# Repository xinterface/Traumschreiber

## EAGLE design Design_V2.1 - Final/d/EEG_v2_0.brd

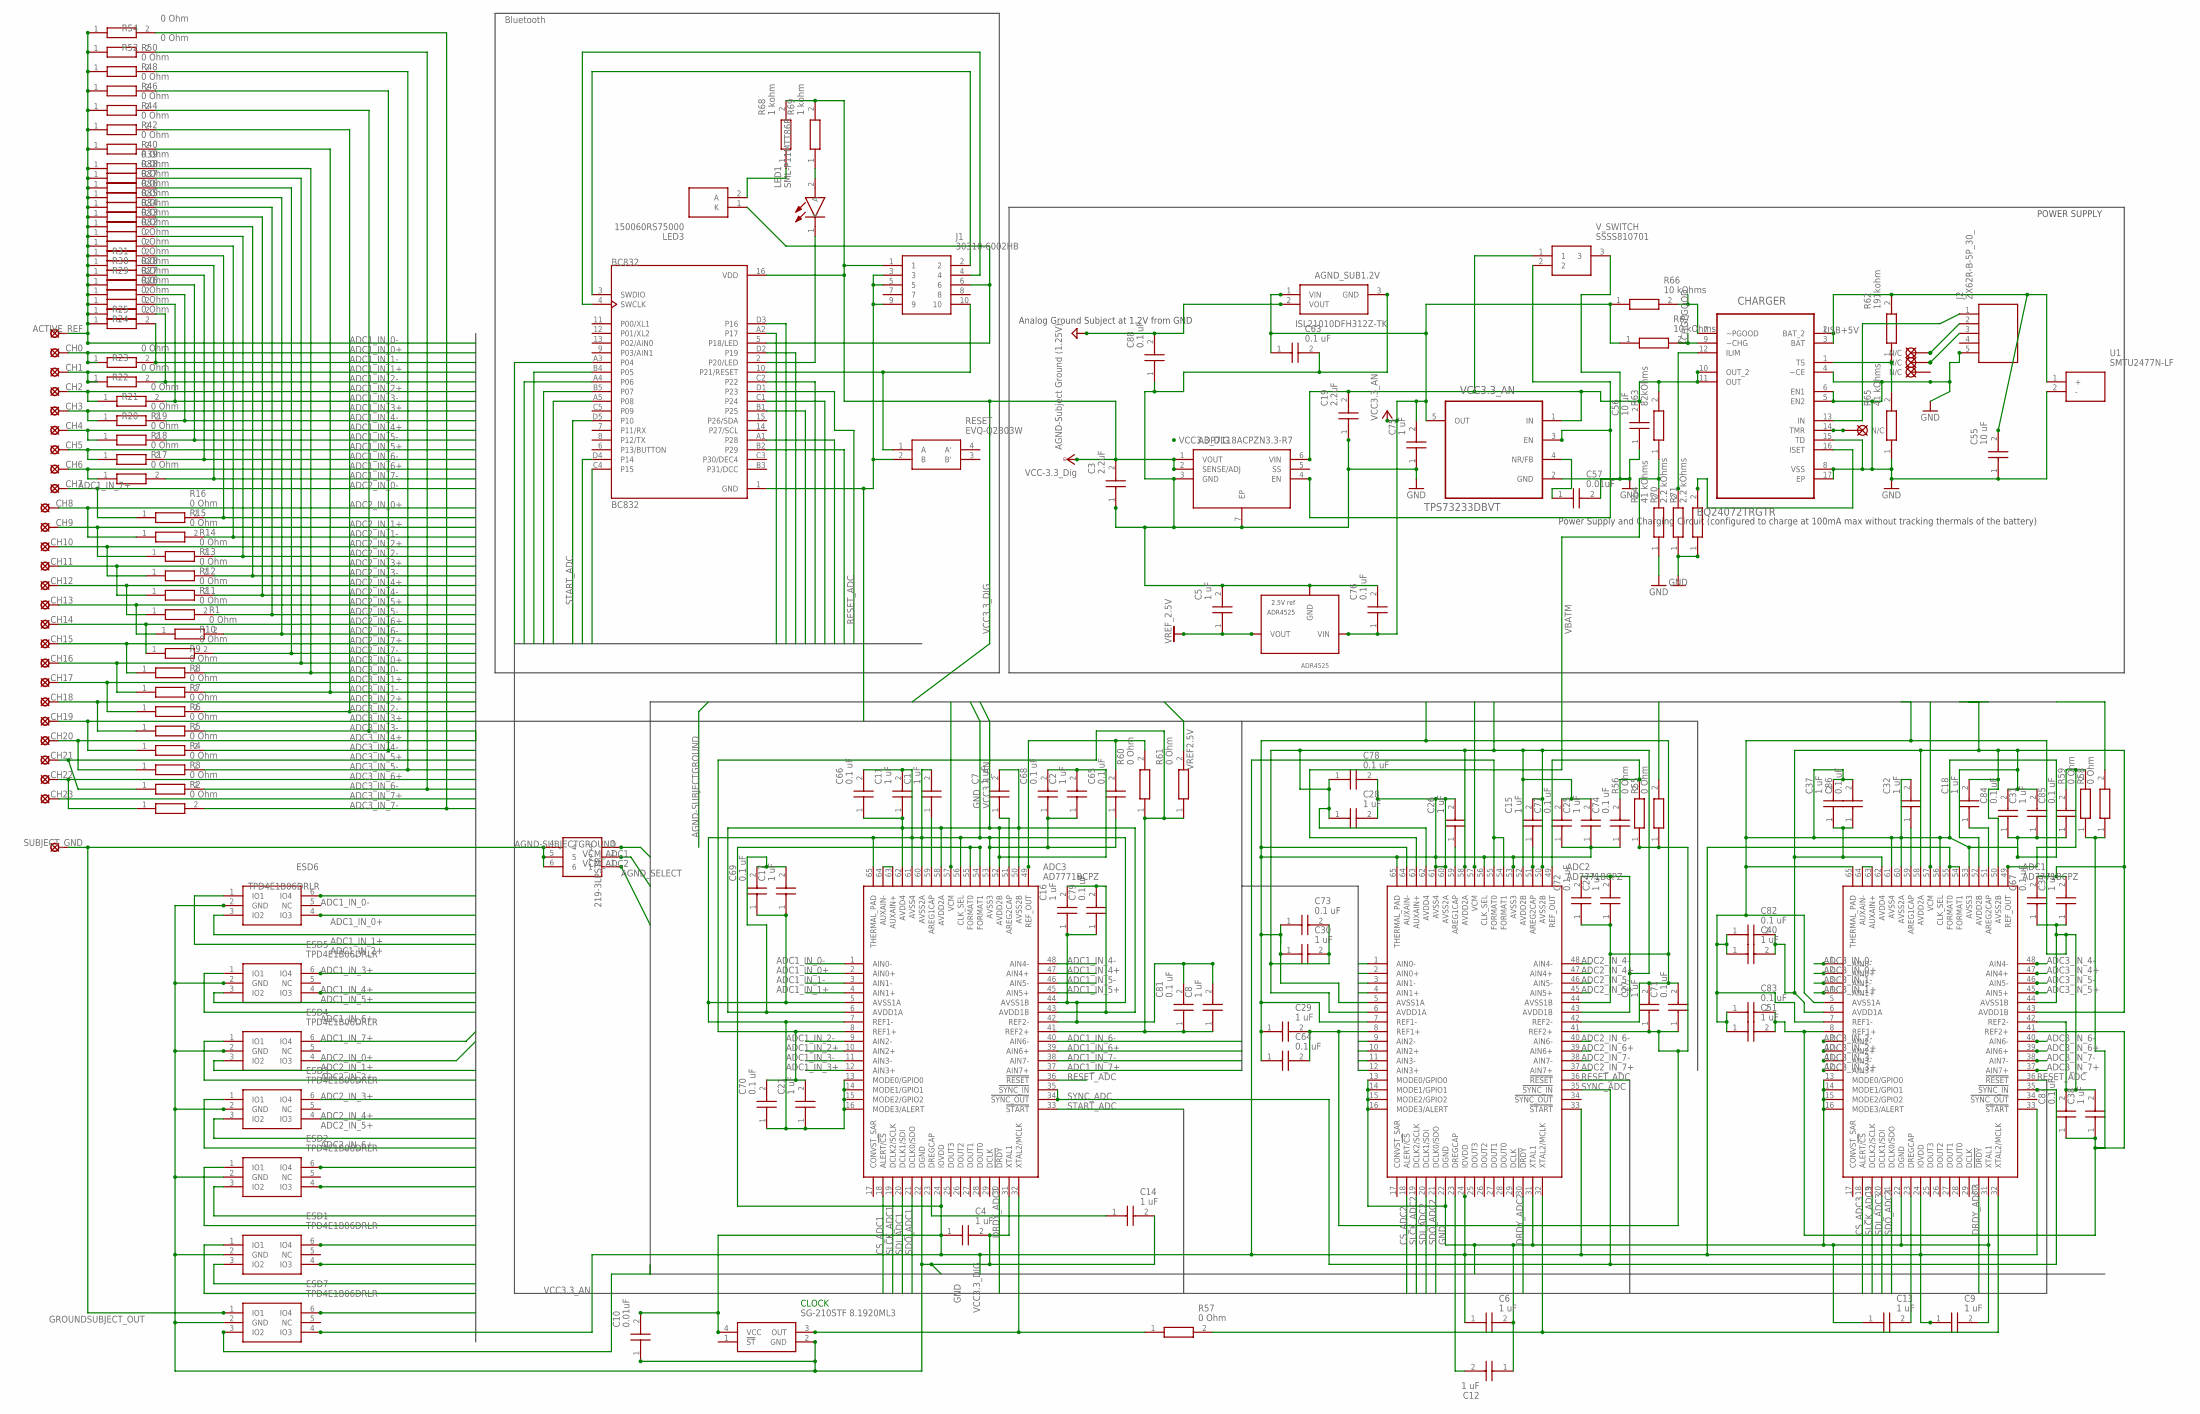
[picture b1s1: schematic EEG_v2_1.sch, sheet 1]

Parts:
ACTIVE_REF: SE11
ADC1, ADC2, ADC3: AD7771BCPZ; QFN50P900X900X80-65N
ADR4525: ADR4525; SOIC-8
AGND_SELECT: 219-3LPSTR; 2193LPSTR
AGND_SUB1.2V: ISL21010DFH312Z-TK; SOT95P237X112-3N
BC832: BC832; XCVR_BC832
C1, C2, C4, C5, C6, C7, C8, C9, C11, C12, C13, C14, C15, C16, C17, C18, C21, C24, C25, C26, C27, C28, C29, C30, C31, C32, C37, C38, C39, C40, C51: 1 uF; CAPC1005X33N
C3, C19: 2.2uF; CAPC0603X33N
C10, C57: 0.01uF; CAPC0402X22N
C55, C56: 10 uF; CAPC1608X100N
C63, C64, C65, C66, C67, C68, C69, C70, C71, C72, C73, C74, C76, C77, C78, C79, C81, C82, C83, C84, C85, C86, C87, C88: 0.1 uF; CAPC0402X22N
C75: 1 uF; CAPC0402X22N
CH0, CH1, CH2, CH3, CH4, CH5, CH6, CH7, CH8, CH9, CH10, CH11, CH12, CH13, CH14, CH15, CH16, CH17, CH18, CH19, CH20, CH21, CH22, CH23: SE11
CHARGER: BQ24072TRGTR; QFN50P300X300X100-17N
CLOCK: SG-210STF 8.1920ML3; SG-210STF8.1920ML
ESD1, ESD2, ESD3, ESD4, ESD5, ESD6, ESD7: TPD4E1B06DRLR; SOP50P160X60-6N
J1: 30310-6002HB; SHDR10W64P254_2X5_2030X878X930
J2: ZX62R-B-5P_30_; ZX62R-B-5P(30)
LED1: SML-P11MTT86R; LEDC1006X25N
LED3: 150060RS75000; LEDC1608X80N
R1, R2, R3, R4, R5, R6, R7, R8, R9, R10, R11, R12, R13, R14, R15, R16, R17, R18, R19, R20, R21, R22, R23, R24, R25, R26, R27, R28, R29, R30, R31, R32, R33, R34, R35, R36, R37, R38, R39, R40, R42, R44, R46, R48, R50, R52, R54, R55, R56, R57, R58, R59, R60, R61: 0 Ohm; RESC1608X55N
R62: 191kohm; RESC0603X26N
R63: 82kOhms; RESC1608X55N
R64, R65: 41 kOhms; RESC0603X28N
R66, R67: 10 kOhms; RESC0402X15N
R68, R69: 1 kohm; RESC0603X26N
R70, R71: 2.2 kOhms; RESC3225X70N
RESET: EVQ-Q2B03W; EVQQ2
SUBJECT_GND: SE11
U1: SMTU2477N-LF; SMTU2477NLF
VCC3.3_AN: TPS73233DBVT; SOT95P280X145-5N
VCC3.3_DIG: ADP7118ACPZN3.3-R7; SON65P200X200X65-7N
V_SWITCH: SSSS810701

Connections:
-CHG: CHARGER.9 (~CHG), R67.2
-PGOOD: CHARGER.7 (~PGOOD), R66.2
ADC1_IN_0+: ADC3.2 (AIN0+), CH0.MP, ESD6.4 (IO3), R23.1
ADC1_IN_0-: ACTIVE_REF.MP, ADC3.1 (AIN0-), ESD6.6 (IO4), R24.1, R25.1, R26.1, R27.1, R28.1, R29.1, R30.1, R31.1, R32.1, R33.1, R34.1, R35.1, R36.1, R37.1, R38.1, R39.1, R40.1, R42.1, R44.1, R46.1, R48.1, R50.1, R52.1, R54.1
ADC1_IN_1+: ADC3.4 (AIN1+), CH1.MP, ESD6.3 (IO2), R22.1
ADC1_IN_1-: ADC3.3 (AIN1-), R23.2, R24.2
ADC1_IN_2+: ADC3.10 (AIN2+), CH2.MP, ESD6.1 (IO1), R21.1
ADC1_IN_2-: ADC3.9 (AIN2-), R22.2, R25.2
ADC1_IN_3+: ADC3.12 (AIN3+), CH3.MP, ESD5.6 (IO4), R20.1
ADC1_IN_3-: ADC3.11 (AIN3-), R21.2, R26.2
ADC1_IN_4+: ADC3.47 (AIN4+), CH4.MP, ESD5.4 (IO3), R19.1
ADC1_IN_4-: ADC3.48 (AIN4-), R20.2, R27.2
ADC1_IN_5+: ADC3.45 (AIN5+), CH5.MP, ESD5.3 (IO2), R18.1
ADC1_IN_5-: ADC3.46 (AIN5-), R19.2, R28.2
ADC1_IN_6+: ADC3.39 (AIN6+), CH6.MP, ESD5.1 (IO1), R17.1
ADC1_IN_6-: ADC3.40 (AIN6-), R18.2, R29.2
ADC1_IN_7+: ADC3.37 (AIN7+), CH7.MP, ESD4.4 (IO3), R16.1
ADC1_IN_7-: ADC3.38 (AIN7-), R17.2, R30.2
ADC2_IN_0+: ADC2.2 (AIN0+), CH8.MP, ESD4.6 (IO4), R15.1
ADC2_IN_0-: ADC2.1 (AIN0-), R16.2, R31.2
ADC2_IN_1+: ADC2.4 (AIN1+), CH9.MP, ESD4.3 (IO2), R14.1
ADC2_IN_1-: ADC2.3 (AIN1-), R15.2, R32.2
ADC2_IN_2+: ADC2.10 (AIN2+), CH10.MP, ESD4.1 (IO1), R13.1
ADC2_IN_2-: ADC2.9 (AIN2-), R14.2, R33.2
ADC2_IN_3+: ADC2.12 (AIN3+), CH11.MP, ESD3.4 (IO3), R12.1
ADC2_IN_3-: ADC2.11 (AIN3-), R13.2, R34.2
ADC2_IN_4+: ADC2.47 (AIN4+), CH12.MP, ESD3.6 (IO4), R11.1
ADC2_IN_4-: ADC2.48 (AIN4-), R12.2, R35.2
ADC2_IN_5+: ADC2.45 (AIN5+), CH13.MP, ESD3.3 (IO2), R1.1
ADC2_IN_5-: ADC2.46 (AIN5-), R11.2, R36.2
ADC2_IN_6+: ADC2.39 (AIN6+), CH14.MP, ESD3.1 (IO1), R10.1
ADC2_IN_6-: ADC2.40 (AIN6-), R1.2, R37.2
ADC2_IN_7+: ADC2.37 (AIN7+), CH15.MP, ESD2.6 (IO4), R9.1
ADC2_IN_7-: ADC2.38 (AIN7-), R10.2, R38.2
ADC3_IN_0+: ADC1.2 (AIN0+), CH16.MP, ESD2.4 (IO3), R8.1, R39.2
ADC3_IN_0-: ADC1.1 (AIN0-), R9.2, R40.2
ADC3_IN_1+: ADC1.4 (AIN1+), CH17.MP, ESD2.3 (IO2), R7.1
ADC3_IN_1-: ADC1.3 (AIN1-), R8.2, R42.2
ADC3_IN_2+: ADC1.10 (AIN2+), CH18.MP, ESD2.1 (IO1), R6.1
ADC3_IN_2-: ADC1.9 (AIN2-), R7.2, R44.2
ADC3_IN_3+: ADC1.12 (AIN3+), CH19.MP, ESD1.6 (IO4), R5.1
ADC3_IN_3-: ADC1.11 (AIN3-), R6.2, R46.2
ADC3_IN_4+: ADC1.47 (AIN4+), CH20.MP, ESD1.4 (IO3), R4.1
ADC3_IN_4-: ADC1.48 (AIN4-), R5.2, R48.2
ADC3_IN_5+: ADC1.45 (AIN5+), CH21.MP, ESD1.3 (IO2), R3.1
ADC3_IN_5-: ADC1.46 (AIN5-), R4.2, R50.2
ADC3_IN_6+: ADC1.39 (AIN6+), CH22.MP, ESD1.1 (IO1), R2.1
ADC3_IN_6-: ADC1.40 (AIN6-), R3.2, R52.2
ADC3_IN_7+: ADC1.37 (AIN7+), CH23.MP, ESD7.6 (IO4)
ADC3_IN_7-: ADC1.38 (AIN7-), R2.2, R54.2
AGND-SUBJECTGROUND: AGND_SELECT.3, AGND_SUB1.2V.2 (VOUT), C88.2
CS_ADC1: ADC3.18 (ALERT/!CS), BC832.A4 (P06)
CS_ADC2: ADC2.18 (ALERT/!CS), BC832.A5 (P08)
CS_ADC3: ADC1.18 (ALERT/!CS), BC832.C1 (P24)
DRDY_ADC1: ADC3.30 (!DRDY), BC832.A2 (P17)
DRDY_ADC2: ADC2.30 (!DRDY), BC832.D4 (P14)
DRDY_ADC3: ADC1.30 (!DRDY), BC832.B1 (P25)
GND: ADC1.5 (AVSS1A), ADC1.7 (REF1-), ADC1.13 (MODE0/GPIO0), ADC1.14 (MODE1/GPIO1), ADC1.15 (MODE2/GPIO2), ADC1.16 (MODE3/ALERT), ADC1.22 (DGND), ADC1.31 (XTAL1), ADC1.42 (REF2-), ADC1.44 (AVSS1B), ADC1.53 (AVSS3), ADC1.56 (CLK_SEL), ADC1.60 (AVSS2A), ADC1.61 (AVSS4), ADC1.65 (THERMAL_PAD), ADC2.5 (AVSS1A), ADC2.7 (REF1-), ADC2.13 (MODE0/GPIO0), ADC2.14 (MODE1/GPIO1), ADC2.15 (MODE2/GPIO2), ADC2.16 (MODE3/ALERT), ADC2.22 (DGND), ADC2.31 (XTAL1), ADC2.42 (REF2-), ADC2.44 (AVSS1B), ADC2.53 (AVSS3), ADC2.56 (CLK_SEL), ADC2.60 (AVSS2A), ADC2.61 (AVSS4), ADC2.64 (AUXAIN-), ADC2.65 (THERMAL_PAD), ADC3.5 (AVSS1A), ADC3.7 (REF1-), ADC3.13 (MODE0/GPIO0), ADC3.14 (MODE1/GPIO1), ADC3.15 (MODE2/GPIO2), ADC3.16 (MODE3/ALERT), ADC3.22 (DGND), ADC3.31 (XTAL1), ADC3.42 (REF2-), ADC3.44 (AVSS1B), ADC3.53 (AVSS3), ADC3.56 (CLK_SEL), ADC3.60 (AVSS2A), ADC3.61 (AVSS4), ADC3.65 (THERMAL_PAD), ADR4525.4 (GND), AGND_SUB1.2V.3 (GND), BC832.1 (GND), C1.2, C2.1, C3.1, C4.2, C5.2, C6.2, C8.2, C9.2, C10.1, C11.2, C12.1, C13.1, C14.2, C16.1, C17.1, C19.1, C21.1, C24.1, C25.1, C26.2, C27.2, C28.2, C29.1, C30.1, C31.1, C32.2, C37.2, C38.2, C39.1, C40.1, C51.1, C55.1, C56.1, C57.2, C63.2, C64.1, C65.1, C66.2, C67.1, C68.1, C69.1, C70.1, C71.2, C72.1, C73.1, C74.1, C75.1, C76.2, C77.1, C78.2, C79.1, C81.2, C82.1, C83.1, C84.1, C85.1, C86.2, C87.2, C88.1, CHARGER.4 (~CE), CHARGER.5 (EN2), CHARGER.6 (EN1), CHARGER.8 (VSS), CHARGER.15 (TD), CHARGER.17 (EP), CLOCK.2 (GND), ESD1.2 (GND), ESD2.2 (GND), ESD3.2 (GND), ESD4.2 (GND), ESD5.2 (GND), ESD6.2 (GND), ESD7.2 (GND), J1.3, J1.5, J1.9, J2.5, R64.1, R65.1, R70.1, R71.1, RESET.2 (B), U1.2 (-), VCC3.3_AN.2 (GND), VCC3.3_DIG.3 (GND), VCC3.3_DIG.7 (EP), V_SWITCH.3; also elsewhere on the board
GROUNDSUBJECT_OUT: AGND_SELECT.4, AGND_SELECT.5, AGND_SELECT.6, ESD7.1 (IO1), SUBJECT_GND.MP
unnamed: ADC3.59 (AREG1CAP), C1.1
unnamed: ADC2.23 (DREGCAP), C12.2
unnamed: ADC2.49 (REF_OUT), C74.2, R56.2
unnamed: ADC1.49 (REF_OUT), C85.2, R59.2
unnamed: BC832.5 (P18/LED), J1.6, LED3.1 (K)
unnamed: BC832.2 (P20/LED), LED1.1 (K)
unnamed: ADC3.63 (AUXAIN+), ADC3.64 (AUXAIN-)
unnamed: ADC3.51 (AREG2CAP), C7.1
unnamed: VCC3.3_AN.3 (EN), VCC3.3_DIG.4 (EN), V_SWITCH.2
unnamed: LED3.2 (A), R68.1
unnamed: LED1.2 (A), R69.1
unnamed: BC832.3 (SWDIO), J1.2
unnamed: ADC2.51 (AREG2CAP), C15.1
unnamed: ADC3.23 (DREGCAP), C14.1
unnamed: BC832.4 (SWCLK), J1.4
unnamed: ADC1.23 (DREGCAP), C13.2
unnamed: BC832.10 (P21/RESET), J1.10, RESET.1 (A)
unnamed: C19.2, C56.2, CHARGER.10 (OUT_2), CHARGER.11 (OUT), R63.2, VCC3.3_AN.1 (IN), VCC3.3_DIG.6 (VIN), V_SWITCH.1
unnamed: C57.1, VCC3.3_AN.4 (NR/FB)
unnamed: ADC1.63 (AUXAIN+), ADC1.64 (AUXAIN-)
unnamed: ADC1.59 (AREG1CAP), C32.1
unnamed: ADC2.59 (AREG1CAP), C26.1
unnamed: ADC1.51 (AREG2CAP), C18.1
unnamed: ADC2.8 (REF1+), ADC2.41 (REF2+), C27.1, C29.2, C64.2, C71.1, R55.1, R56.1
unnamed: ADC1.8 (REF1+), ADC1.41 (REF2+), C38.1, C51.2, C83.2, C87.1, R58.1, R59.1
unnamed: CHARGER.1 (TS), R62.1, R65.2
unnamed 86: C55.2, CHARGER.2 (BAT_2), CHARGER.3 (BAT), R62.2, U1.1 (+); also elsewhere on the board
unnamed: CHARGER.16 (ISET), R71.2
unnamed: CHARGER.12 (ILIM), R70.2
REF_ADC1_IN: ADC3.8 (REF1+), ADC3.41 (REF2+), C8.1, C21.2, C70.2, C81.1, R60.1, R61.1
REF_ADC1_OUT: ADC3.49 (REF_OUT), C65.2, R60.2
RESET_ADC: ADC1.36 (!RESET), ADC2.36 (!RESET), ADC3.36 (!RESET), BC832.D1 (P23)
SDI_ADC1: ADC3.20 (DCLK1/SDI), BC832.C4 (P15)
SDI_ADC2: ADC2.20 (DCLK1/SDI), BC832.B5 (P07)
SDI_ADC3: ADC1.20 (DCLK1/SDI), BC832.A1 (P28)
SDO_ADC1: ADC3.21 (DCLK0/SDO), BC832.D3 (P16)
SDO_ADC2: ADC2.21 (DCLK0/SDO), BC832.B4 (P05)
SDO_ADC3: ADC1.21 (DCLK0/SDO), BC832.B2 (P29)
SLCK_ADC1: ADC3.19 (DCLK2/SCLK), BC832.A3 (P04)
SLCK_ADC2: ADC2.19 (DCLK2/SCLK), BC832.D2 (P19)
SLCK_ADC3: ADC1.19 (DCLK2/SCLK), BC832.C2 (P22)
START_ADC: ADC3.33 (!START), BC832.D5 (P10)
SYNC_ADC: ADC1.35 (!SYNC_IN), ADC2.35 (!SYNC_IN), ADC3.34 (!SYNC_OUT), ADC3.35 (!SYNC_IN)
USB+5V: CHARGER.13 (IN), J2.1; also elsewhere on the board
VBATM: ADC2.63 (AUXAIN+), R63.1, R64.2
VCC3.3_AN: ADC1.6 (AVDD1A), ADC1.43 (AVDD1B), ADC1.50 (AVSS2B), ADC1.52 (AVDD2B), ADC1.58 (AVDD2A), ADC1.62 (AVDD4), ADC2.6 (AVDD1A), ADC2.43 (AVDD1B), ADC2.50 (AVSS2B), ADC2.52 (AVDD2B), ADC2.58 (AVDD2A), ADC2.62 (AVDD4), ADC3.6 (AVDD1A), ADC3.43 (AVDD1B), ADC3.50 (AVSS2B), ADC3.52 (AVDD2B), ADC3.58 (AVDD2A), ADC3.62 (AVDD4), ADR4525.2 (VIN), AGND_SUB1.2V.1 (VIN), C2.2, C7.2, C11.1, C15.2, C16.2, C17.2, C18.2, C24.2, C25.2, C28.1, C30.2, C31.2, C37.1, C39.2, C40.2, C63.1, C66.1, C67.2, C68.2, C69.2, C72.2, C73.2, C75.2, C76.1, C77.2, C78.1, C79.2, C82.2, C84.2, C86.1, ESD7.3 (IO2), R66.1, R67.1, VCC3.3_AN.5 (OUT)
VCC3.3_DIG: ADC1.24 (IOVDD), ADC1.33 (!START), ADC1.54 (FORMAT1), ADC1.55 (FORMAT0), ADC2.24 (IOVDD), ADC2.33 (!START), ADC2.54 (FORMAT1), ADC2.55 (FORMAT0), ADC3.24 (IOVDD), ADC3.54 (FORMAT1), ADC3.55 (FORMAT0), BC832.16 (VDD), C3.2, C4.1, C6.1, C9.1, C10.2, CLOCK.4 (VCC), ESD7.4 (IO3), J1.1, R68.2, R69.2, VCC3.3_DIG.1 (VOUT), VCC3.3_DIG.2 (SENSE/ADJ)
VCM_ADC1: ADC3.57 (VCM), AGND_SELECT.2
VCM_ADC2: ADC2.57 (VCM), AGND_SELECT.1
VCM_ADC3: ADC1.57 (VCM)
VREF2.5V: ADR4525.6 (VOUT), C5.1, R55.2, R58.2, R61.2
XTAL_OUT: ADC3.32 (XTAL2/MCLK), CLOCK.3 (OUT), R57.1
XTAL_OUT_SWITCHED: ADC1.32 (XTAL2/MCLK), ADC2.32 (XTAL2/MCLK), R57.2

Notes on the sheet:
Analog Ground Subject at 1.2V from GND
Power Supply and Charging Circuit (configured to charge at 100mA max without tracking thermals of the battery)
POWER SUPPLY
Bluetooth

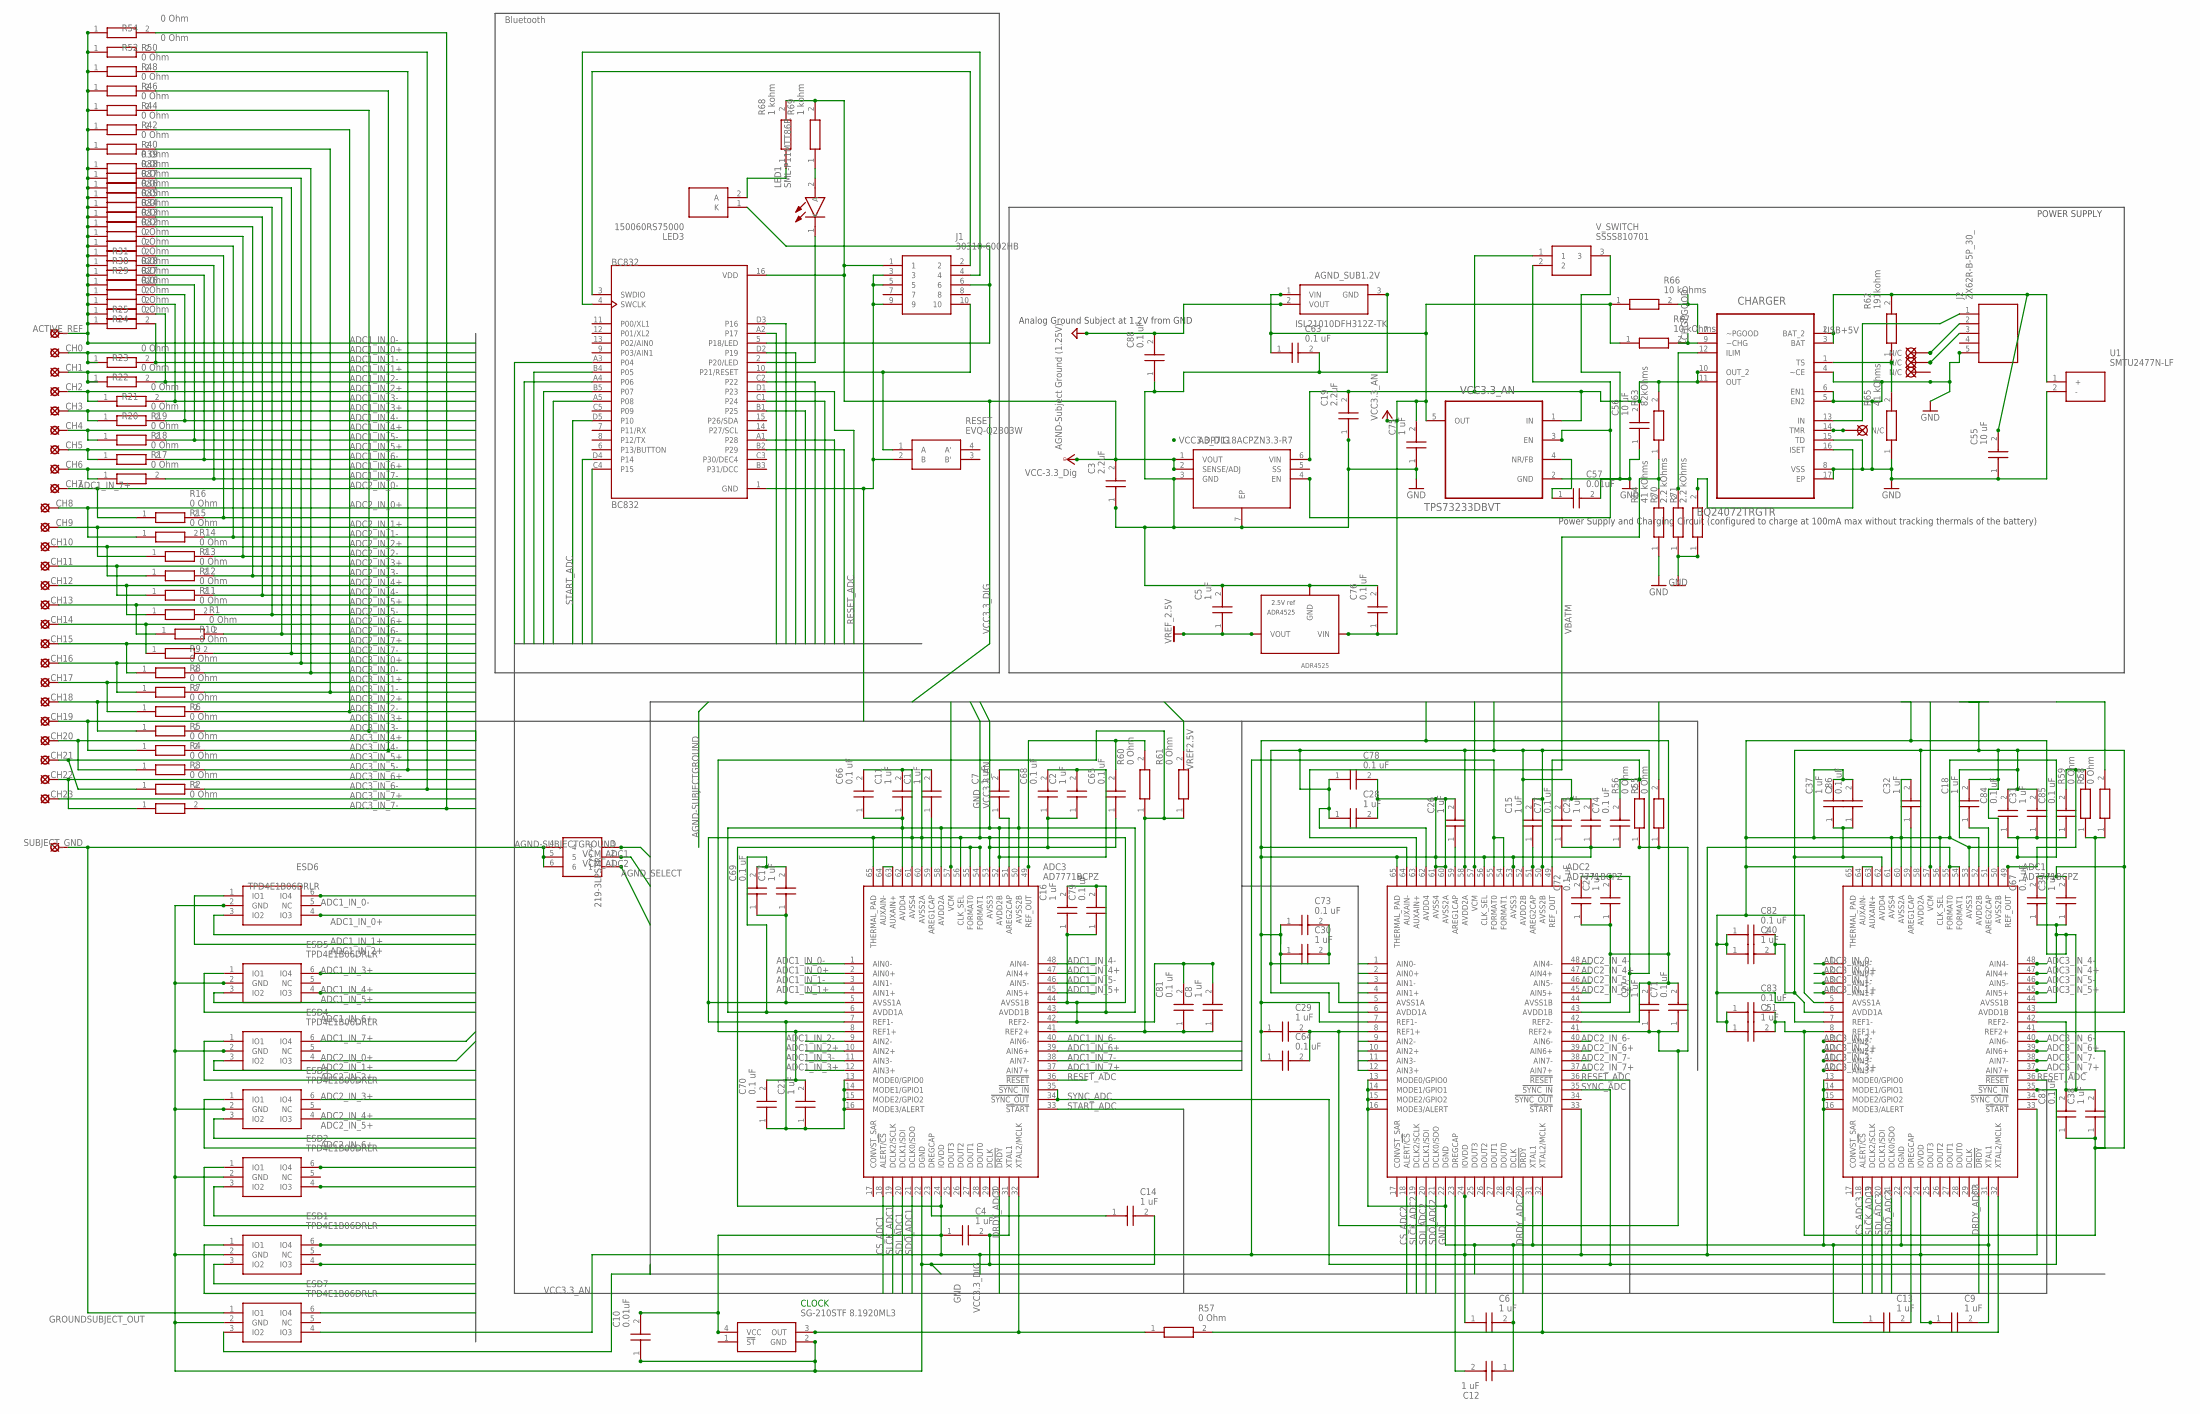
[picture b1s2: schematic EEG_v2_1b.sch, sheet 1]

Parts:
ACTIVE_REF: SE11
ADC1, ADC2, ADC3: AD7771BCPZ; QFN50P900X900X80-65N
ADR4525: ADR4525; SOIC-8
AGND_SELECT: 219-3LPSTR; 2193LPSTR
AGND_SUB1.2V: ISL21010DFH312Z-TK; SOT95P237X112-3N
BC832: BC832; XCVR_BC832
C1, C2, C4, C5, C6, C7, C8, C9, C11, C12, C13, C14, C15, C16, C17, C18, C21, C24, C25, C26, C27, C28, C29, C30, C31, C32, C37, C38, C39, C40, C51: 1 uF; CAPC1005X33N
C3, C19: 2.2uF; CAPC0603X33N
C10, C57: 0.01uF; CAPC0402X22N
C55, C56: 10 uF; CAPC1608X100N
C63, C64, C65, C66, C67, C68, C69, C70, C71, C72, C73, C74, C76, C77, C78, C79, C81, C82, C83, C84, C85, C86, C87, C88: 0.1 uF; CAPC0402X22N
C75: 1 uF; CAPC0402X22N
CH0, CH1, CH2, CH3, CH4, CH5, CH6, CH7, CH8, CH9, CH10, CH11, CH12, CH13, CH14, CH15, CH16, CH17, CH18, CH19, CH20, CH21, CH22, CH23: SE11
CHARGER: BQ24072TRGTR; QFN50P300X300X100-17N
CLOCK: SG-210STF 8.1920ML3; SG-210STF8.1920ML
ESD1, ESD2, ESD3, ESD4, ESD5, ESD6, ESD7: TPD4E1B06DRLR; SOP50P160X60-6N
J1: 30310-6002HB; SHDR10W64P254_2X5_2030X878X930
J2: ZX62R-B-5P_30_; ZX62R-B-5P(30)
LED1: SML-P11MTT86R; LEDC1006X25N
LED3: 150060RS75000; LEDC1608X80N
R1, R2, R3, R4, R5, R6, R7, R8, R9, R10, R11, R12, R13, R14, R15, R16, R17, R18, R19, R20, R21, R22, R23, R24, R25, R26, R27, R28, R29, R30, R31, R32, R33, R34, R35, R36, R37, R38, R39, R40, R42, R44, R46, R48, R50, R52, R54, R55, R56, R57, R58, R59, R60, R61: 0 Ohm; RESC1608X55N
R62: 191kohm; RESC0603X26N
R63: 82kOhms; RESC1608X55N
R64, R65: 41 kOhms; RESC0603X28N
R66, R67: 10 kOhms; RESC0402X15N
R68, R69: 1 kohm; RESC0603X26N
R70, R71: 2.2 kOhms; RESC3225X70N
RESET: EVQ-Q2B03W; EVQQ2
SUBJECT_GND: SE11
U1: SMTU2477N-LF; SMTU2477NLF
VCC3.3_AN: TPS73233DBVT; SOT95P280X145-5N
VCC3.3_DIG: ADP7118ACPZN3.3-R7; SON65P200X200X65-7N
V_SWITCH: SSSS810701

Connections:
-CHG: CHARGER.9 (~CHG), R67.2
-PGOOD: CHARGER.7 (~PGOOD), R66.2
ADC1_IN_0+: ADC3.2 (AIN0+), CH0.MP, ESD6.4 (IO3), R23.1
ADC1_IN_0-: ACTIVE_REF.MP, ADC3.1 (AIN0-), ESD6.6 (IO4), R24.1, R25.1, R26.1, R27.1, R28.1, R29.1, R30.1, R31.1, R32.1, R33.1, R34.1, R35.1, R36.1, R37.1, R38.1, R39.1, R40.1, R42.1, R44.1, R46.1, R48.1, R50.1, R52.1, R54.1
ADC1_IN_1+: ADC3.4 (AIN1+), CH1.MP, ESD6.3 (IO2), R22.1
ADC1_IN_1-: ADC3.3 (AIN1-), R23.2, R24.2
ADC1_IN_2+: ADC3.10 (AIN2+), CH2.MP, ESD6.1 (IO1), R21.1
ADC1_IN_2-: ADC3.9 (AIN2-), R22.2, R25.2
ADC1_IN_3+: ADC3.12 (AIN3+), CH3.MP, ESD5.6 (IO4), R20.1
ADC1_IN_3-: ADC3.11 (AIN3-), R21.2, R26.2
ADC1_IN_4+: ADC3.47 (AIN4+), CH4.MP, ESD5.4 (IO3), R19.1
ADC1_IN_4-: ADC3.48 (AIN4-), R20.2, R27.2
ADC1_IN_5+: ADC3.45 (AIN5+), CH5.MP, ESD5.3 (IO2), R18.1
ADC1_IN_5-: ADC3.46 (AIN5-), R19.2, R28.2
ADC1_IN_6+: ADC3.39 (AIN6+), CH6.MP, ESD5.1 (IO1), R17.1
ADC1_IN_6-: ADC3.40 (AIN6-), R18.2, R29.2
ADC1_IN_7+: ADC3.37 (AIN7+), CH7.MP, ESD4.4 (IO3), R16.1
ADC1_IN_7-: ADC3.38 (AIN7-), R17.2, R30.2
ADC2_IN_0+: ADC2.2 (AIN0+), CH8.MP, ESD4.6 (IO4), R15.1
ADC2_IN_0-: ADC2.1 (AIN0-), R16.2, R31.2
ADC2_IN_1+: ADC2.4 (AIN1+), CH9.MP, ESD4.3 (IO2), R14.1
ADC2_IN_1-: ADC2.3 (AIN1-), R15.2, R32.2
ADC2_IN_2+: ADC2.10 (AIN2+), CH10.MP, ESD4.1 (IO1), R13.1
ADC2_IN_2-: ADC2.9 (AIN2-), R14.2, R33.2
ADC2_IN_3+: ADC2.12 (AIN3+), CH11.MP, ESD3.4 (IO3), R12.1
ADC2_IN_3-: ADC2.11 (AIN3-), R13.2, R34.2
ADC2_IN_4+: ADC2.47 (AIN4+), CH12.MP, ESD3.6 (IO4), R11.1
ADC2_IN_4-: ADC2.48 (AIN4-), R12.2, R35.2
ADC2_IN_5+: ADC2.45 (AIN5+), CH13.MP, ESD3.3 (IO2), R1.1
ADC2_IN_5-: ADC2.46 (AIN5-), R11.2, R36.2
ADC2_IN_6+: ADC2.39 (AIN6+), CH14.MP, ESD3.1 (IO1), R10.1
ADC2_IN_6-: ADC2.40 (AIN6-), R1.2, R37.2
ADC2_IN_7+: ADC2.37 (AIN7+), CH15.MP, ESD2.6 (IO4), R9.1
ADC2_IN_7-: ADC2.38 (AIN7-), R10.2, R38.2
ADC3_IN_0+: ADC1.2 (AIN0+), CH16.MP, ESD2.4 (IO3), R8.1, R39.2
ADC3_IN_0-: ADC1.1 (AIN0-), R9.2, R40.2
ADC3_IN_1+: ADC1.4 (AIN1+), CH17.MP, ESD2.3 (IO2), R7.1
ADC3_IN_1-: ADC1.3 (AIN1-), R8.2, R42.2
ADC3_IN_2+: ADC1.10 (AIN2+), CH18.MP, ESD2.1 (IO1), R6.1
ADC3_IN_2-: ADC1.9 (AIN2-), R7.2, R44.2
ADC3_IN_3+: ADC1.12 (AIN3+), CH19.MP, ESD1.6 (IO4), R5.1
ADC3_IN_3-: ADC1.11 (AIN3-), R6.2, R46.2
ADC3_IN_4+: ADC1.47 (AIN4+), CH20.MP, ESD1.4 (IO3), R4.1
ADC3_IN_4-: ADC1.48 (AIN4-), R5.2, R48.2
ADC3_IN_5+: ADC1.45 (AIN5+), CH21.MP, ESD1.3 (IO2), R3.1
ADC3_IN_5-: ADC1.46 (AIN5-), R4.2, R50.2
ADC3_IN_6+: ADC1.39 (AIN6+), CH22.MP, ESD1.1 (IO1), R2.1
ADC3_IN_6-: ADC1.40 (AIN6-), R3.2, R52.2
ADC3_IN_7+: ADC1.37 (AIN7+), CH23.MP, ESD7.6 (IO4)
ADC3_IN_7-: ADC1.38 (AIN7-), R2.2, R54.2
AGND-SUBJECTGROUND: AGND_SELECT.3, AGND_SUB1.2V.2 (VOUT), C88.2
CS_ADC1: ADC3.18 (ALERT/!CS), BC832.A4 (P06)
CS_ADC2: ADC2.18 (ALERT/!CS), BC832.A5 (P08)
CS_ADC3: ADC1.18 (ALERT/!CS), BC832.C1 (P24)
DRDY_ADC1: ADC3.30 (!DRDY), BC832.A2 (P17)
DRDY_ADC2: ADC2.30 (!DRDY), BC832.D4 (P14)
DRDY_ADC3: ADC1.30 (!DRDY), BC832.B1 (P25)
GND: ADC1.5 (AVSS1A), ADC1.7 (REF1-), ADC1.13 (MODE0/GPIO0), ADC1.14 (MODE1/GPIO1), ADC1.15 (MODE2/GPIO2), ADC1.16 (MODE3/ALERT), ADC1.22 (DGND), ADC1.31 (XTAL1), ADC1.42 (REF2-), ADC1.44 (AVSS1B), ADC1.53 (AVSS3), ADC1.56 (CLK_SEL), ADC1.60 (AVSS2A), ADC1.61 (AVSS4), ADC1.65 (THERMAL_PAD), ADC2.5 (AVSS1A), ADC2.7 (REF1-), ADC2.13 (MODE0/GPIO0), ADC2.14 (MODE1/GPIO1), ADC2.15 (MODE2/GPIO2), ADC2.16 (MODE3/ALERT), ADC2.22 (DGND), ADC2.31 (XTAL1), ADC2.42 (REF2-), ADC2.44 (AVSS1B), ADC2.53 (AVSS3), ADC2.56 (CLK_SEL), ADC2.60 (AVSS2A), ADC2.61 (AVSS4), ADC2.64 (AUXAIN-), ADC2.65 (THERMAL_PAD), ADC3.5 (AVSS1A), ADC3.7 (REF1-), ADC3.13 (MODE0/GPIO0), ADC3.14 (MODE1/GPIO1), ADC3.15 (MODE2/GPIO2), ADC3.16 (MODE3/ALERT), ADC3.22 (DGND), ADC3.31 (XTAL1), ADC3.42 (REF2-), ADC3.44 (AVSS1B), ADC3.53 (AVSS3), ADC3.56 (CLK_SEL), ADC3.60 (AVSS2A), ADC3.61 (AVSS4), ADC3.65 (THERMAL_PAD), ADR4525.4 (GND), AGND_SUB1.2V.3 (GND), BC832.1 (GND), C1.2, C2.1, C3.1, C4.2, C5.2, C6.2, C8.2, C9.2, C10.1, C11.2, C12.1, C13.1, C14.2, C16.1, C17.1, C19.1, C21.1, C24.1, C25.1, C26.2, C27.2, C28.2, C29.1, C30.1, C31.1, C32.2, C37.2, C38.2, C39.1, C40.1, C51.1, C55.1, C56.1, C57.2, C63.2, C64.1, C65.1, C66.2, C67.1, C68.1, C69.1, C70.1, C71.2, C72.1, C73.1, C74.1, C75.1, C76.2, C77.1, C78.2, C79.1, C81.2, C82.1, C83.1, C84.1, C85.1, C86.2, C87.2, C88.1, CHARGER.4 (~CE), CHARGER.5 (EN2), CHARGER.6 (EN1), CHARGER.8 (VSS), CHARGER.15 (TD), CHARGER.17 (EP), CLOCK.2 (GND), ESD1.2 (GND), ESD2.2 (GND), ESD3.2 (GND), ESD4.2 (GND), ESD5.2 (GND), ESD6.2 (GND), ESD7.2 (GND), J1.3, J1.5, J1.9, J2.5, R64.1, R65.1, R70.1, R71.1, RESET.2 (B), U1.2 (-), VCC3.3_AN.2 (GND), VCC3.3_DIG.3 (GND), VCC3.3_DIG.7 (EP), V_SWITCH.3; also elsewhere on the board
GROUNDSUBJECT_OUT: AGND_SELECT.4, AGND_SELECT.5, AGND_SELECT.6, ESD7.1 (IO1), SUBJECT_GND.MP
unnamed: ADC3.59 (AREG1CAP), C1.1
unnamed: ADC2.23 (DREGCAP), C12.2
unnamed: ADC2.49 (REF_OUT), C74.2, R56.2
unnamed: ADC1.49 (REF_OUT), C85.2, R59.2
unnamed: BC832.5 (P18/LED), J1.6, LED3.1 (K)
unnamed: BC832.2 (P20/LED), LED1.1 (K)
unnamed: ADC3.63 (AUXAIN+), ADC3.64 (AUXAIN-)
unnamed: ADC3.51 (AREG2CAP), C7.1
unnamed: VCC3.3_AN.3 (EN), VCC3.3_DIG.4 (EN), V_SWITCH.2
unnamed: LED3.2 (A), R68.1
unnamed: LED1.2 (A), R69.1
unnamed: BC832.3 (SWDIO), J1.2
unnamed: ADC2.51 (AREG2CAP), C15.1
unnamed: ADC3.23 (DREGCAP), C14.1
unnamed: BC832.4 (SWCLK), J1.4
unnamed: ADC1.23 (DREGCAP), C13.2
unnamed: BC832.10 (P21/RESET), J1.10, RESET.1 (A)
unnamed: C19.2, C56.2, CHARGER.10 (OUT_2), CHARGER.11 (OUT), R63.2, VCC3.3_AN.1 (IN), VCC3.3_DIG.6 (VIN), V_SWITCH.1
unnamed: C57.1, VCC3.3_AN.4 (NR/FB)
unnamed: ADC1.63 (AUXAIN+), ADC1.64 (AUXAIN-)
unnamed: ADC1.59 (AREG1CAP), C32.1
unnamed: ADC2.59 (AREG1CAP), C26.1
unnamed: ADC1.51 (AREG2CAP), C18.1
unnamed: ADC2.8 (REF1+), ADC2.41 (REF2+), C27.1, C29.2, C64.2, C71.1, R55.1, R56.1
unnamed: ADC1.8 (REF1+), ADC1.41 (REF2+), C38.1, C51.2, C83.2, C87.1, R58.1, R59.1
unnamed: CHARGER.1 (TS), R62.1, R65.2
unnamed 86: C55.2, CHARGER.2 (BAT_2), CHARGER.3 (BAT), R62.2, U1.1 (+); also elsewhere on the board
unnamed: CHARGER.16 (ISET), R71.2
unnamed: CHARGER.12 (ILIM), R70.2
REF_ADC1_IN: ADC3.8 (REF1+), ADC3.41 (REF2+), C8.1, C21.2, C70.2, C81.1, R60.1, R61.1
REF_ADC1_OUT: ADC3.49 (REF_OUT), C65.2, R60.2
RESET_ADC: ADC1.36 (!RESET), ADC2.36 (!RESET), ADC3.36 (!RESET), BC832.D1 (P23)
SDI_ADC1: ADC3.20 (DCLK1/SDI), BC832.C4 (P15)
SDI_ADC2: ADC2.20 (DCLK1/SDI), BC832.B5 (P07)
SDI_ADC3: ADC1.20 (DCLK1/SDI), BC832.A1 (P28)
SDO_ADC1: ADC3.21 (DCLK0/SDO), BC832.D3 (P16)
SDO_ADC2: ADC2.21 (DCLK0/SDO), BC832.B4 (P05)
SDO_ADC3: ADC1.21 (DCLK0/SDO), BC832.B2 (P29)
SLCK_ADC1: ADC3.19 (DCLK2/SCLK), BC832.A3 (P04)
SLCK_ADC2: ADC2.19 (DCLK2/SCLK), BC832.D2 (P19)
SLCK_ADC3: ADC1.19 (DCLK2/SCLK), BC832.C2 (P22)
START_ADC: ADC3.33 (!START), BC832.D5 (P10)
SYNC_ADC: ADC1.35 (!SYNC_IN), ADC2.35 (!SYNC_IN), ADC3.34 (!SYNC_OUT), ADC3.35 (!SYNC_IN)
USB+5V: CHARGER.13 (IN), J2.1; also elsewhere on the board
VBATM: ADC2.63 (AUXAIN+), R63.1, R64.2
VCC3.3_AN: ADC1.6 (AVDD1A), ADC1.43 (AVDD1B), ADC1.50 (AVSS2B), ADC1.52 (AVDD2B), ADC1.58 (AVDD2A), ADC1.62 (AVDD4), ADC2.6 (AVDD1A), ADC2.43 (AVDD1B), ADC2.50 (AVSS2B), ADC2.52 (AVDD2B), ADC2.58 (AVDD2A), ADC2.62 (AVDD4), ADC3.6 (AVDD1A), ADC3.43 (AVDD1B), ADC3.50 (AVSS2B), ADC3.52 (AVDD2B), ADC3.58 (AVDD2A), ADC3.62 (AVDD4), ADR4525.2 (VIN), AGND_SUB1.2V.1 (VIN), C2.2, C7.2, C11.1, C15.2, C16.2, C17.2, C18.2, C24.2, C25.2, C28.1, C30.2, C31.2, C37.1, C39.2, C40.2, C63.1, C66.1, C67.2, C68.2, C69.2, C72.2, C73.2, C75.2, C76.1, C77.2, C78.1, C79.2, C82.2, C84.2, C86.1, ESD7.3 (IO2), R66.1, R67.1, VCC3.3_AN.5 (OUT)
VCC3.3_DIG: ADC1.24 (IOVDD), ADC1.33 (!START), ADC1.54 (FORMAT1), ADC1.55 (FORMAT0), ADC2.24 (IOVDD), ADC2.33 (!START), ADC2.54 (FORMAT1), ADC2.55 (FORMAT0), ADC3.24 (IOVDD), ADC3.54 (FORMAT1), ADC3.55 (FORMAT0), BC832.16 (VDD), C3.2, C4.1, C6.1, C9.1, C10.2, CLOCK.4 (VCC), ESD7.4 (IO3), J1.1, R68.2, R69.2, VCC3.3_DIG.1 (VOUT), VCC3.3_DIG.2 (SENSE/ADJ)
VCM_ADC1: ADC3.57 (VCM), AGND_SELECT.2
VCM_ADC2: ADC2.57 (VCM), AGND_SELECT.1
VCM_ADC3: ADC1.57 (VCM)
VREF2.5V: ADR4525.6 (VOUT), C5.1, R55.2, R58.2, R61.2
XTAL_OUT: ADC3.32 (XTAL2/MCLK), CLOCK.3 (OUT), R57.1
XTAL_OUT_SWITCHED: ADC1.32 (XTAL2/MCLK), ADC2.32 (XTAL2/MCLK), R57.2

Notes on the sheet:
Analog Ground Subject at 1.2V from GND
Power Supply and Charging Circuit (configured to charge at 100mA max without tracking thermals of the battery)
POWER SUPPLY
Bluetooth
